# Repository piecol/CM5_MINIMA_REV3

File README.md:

# CM5 MINIMA REV3

## Introduction

The **CM5 MINIMA REV3** is a compact carrier board for the latest Raspberry Pi computing module 5.
It is designed for embedded applications, DIY electronics, and low-power computing projects. Unlike traditional desktop computers, the CM5 is a small, efficient system that integrates essential computing hardware onto a single board. Whether you're a hobbyist, developer, or engineer, this module provides a versatile platform for various applications, including IoT, automation, and custom hardware development.

If you're not familiar with Raspberry Pi or single-board computers (SBCs), think of the CM5 as a miniaturized computer that can handle tasks like data processing, networking, and hardware control, all while fitting in the palm of your hand. 
https://www.raspberrypi.com/products/compute-module-5/?variant=cm5-104032

Get to know the story behind the MINIMA on Hackster.io:

https://www.hackster.io/piecol/tiny-open-source-media-streamer-with-lorawan-what-a98a93

## Designed with KiCad

MINIMA was developed using KiCad, a powerful open-source Electronic Design Automation (EDA) tool. KiCad enables designers to create high-quality PCB layouts and schematics while maintaining full control over their hardware designs. By leveraging open-source tools like KiCad, the CM5 MINIMA REV3 embraces accessibility, collaboration, and innovation in hardware development.

## NextPCB production ready

This project is kindly supported by [NextPCB](https://www.nextpcb.com/), an excellent KiCAD-friendly PCB manufacturer.
Under "nextpcb/production_files" you can find production files to directly place your order.
Explore thier blog https://www.nextpcb.com/blog/exploring-the-cm5-minima-rev3

## Key Features

- **USB-C Power Delivery (PD):** Supports power negotiation for efficient energy use.
- **USB 2.0 Ports:** Connect peripherals such as keyboards, mice, and external storage.
- **Gigabit Ethernet:** High-speed wired networking with a low-profile cutout magjack.
- **HDMI Port:** Output video to external displays for media playback or interface applications.
- **M.2 M Key Slot:** Supports 2230/2242 SSDs for fast storage expansion.
- **CSI/DSI Connector:** Attach camera modules or displays for vision-based applications.
- **LIS3DH STM32 Sensor:** Built-in accelerometer.
- **I2C Connector (3.3V only):** Connect low-power sensors and communication modules.
- **SPI Connector:** Supports high-speed communication with other devices.
- **Fan Connector:** Optional cooling support for high-performance applications.
- **Status LEDs:** Visual indicators for power and system activity.
- **Compact Size:** Measuring only **5.4 × 5.7 cm**, ideal for space-constrained projects.

## Schematics

[PDF SCHEMATICS](https://github.com/piecol/CM5_MINIMA_REV3/blob/main/CM5_MINIMA_3.pdf)

## Getting Started

To use the **CM5 MINIMA REV3**, you'll need:

- A **USB-C power adapter** that supports Power Delivery (PD).
- A **display (HDMI)** and **input devices (USB keyboard/mouse)** for setup.
- A **network connection** (Ethernet or Wi-Fi via an external adapter if needed).

## Flashing OS

To flash an operating system (OS) to the CM5, use the switch located on the bottom of the board to enable flashing mode. It is equivalent to the "Fit nRPI_BOOT to J2 (disable eMMC Boot) on the IO board jumper." on the CM5 IO board.
Please refere to the official guidelines for further instructions:
https://www.raspberrypi.com/documentation/computers/compute-module.html#set-up-the-io-board

## Applications

- **IoT & Smart Devices:** Use sensors and network capabilities to create connected applications.
- **Home Automation:** Control and monitor home devices with minimal power consumption.
- **Embedded Systems:** Develop custom hardware solutions for industrial and consumer electronics.
- **Media Centers:** Play videos and manage digital content on an external display.
- **DIY Projects:** Ideal for makers and educators learning about electronics and programming.

## CNC casing

Custom casing with passive heat-sink was supported by PCBway, grab the .STEP file in the CNC_enclosure folder and order yours.

## Conclusion

The **CM5 MINIMA REV3** is a powerful and flexible computing module that opens up endless possibilities for embedded computing and automation. Whether you're building a smart device, experimenting with sensors, or designing a networked system, this board provides the essential features you need in a compact, energy-efficient form factor.

## **Stackup**:
6L (SIG:PWR | GND | SIG-PWR | PWR | GND | SIG:PWR) 

### If you would like to support me:

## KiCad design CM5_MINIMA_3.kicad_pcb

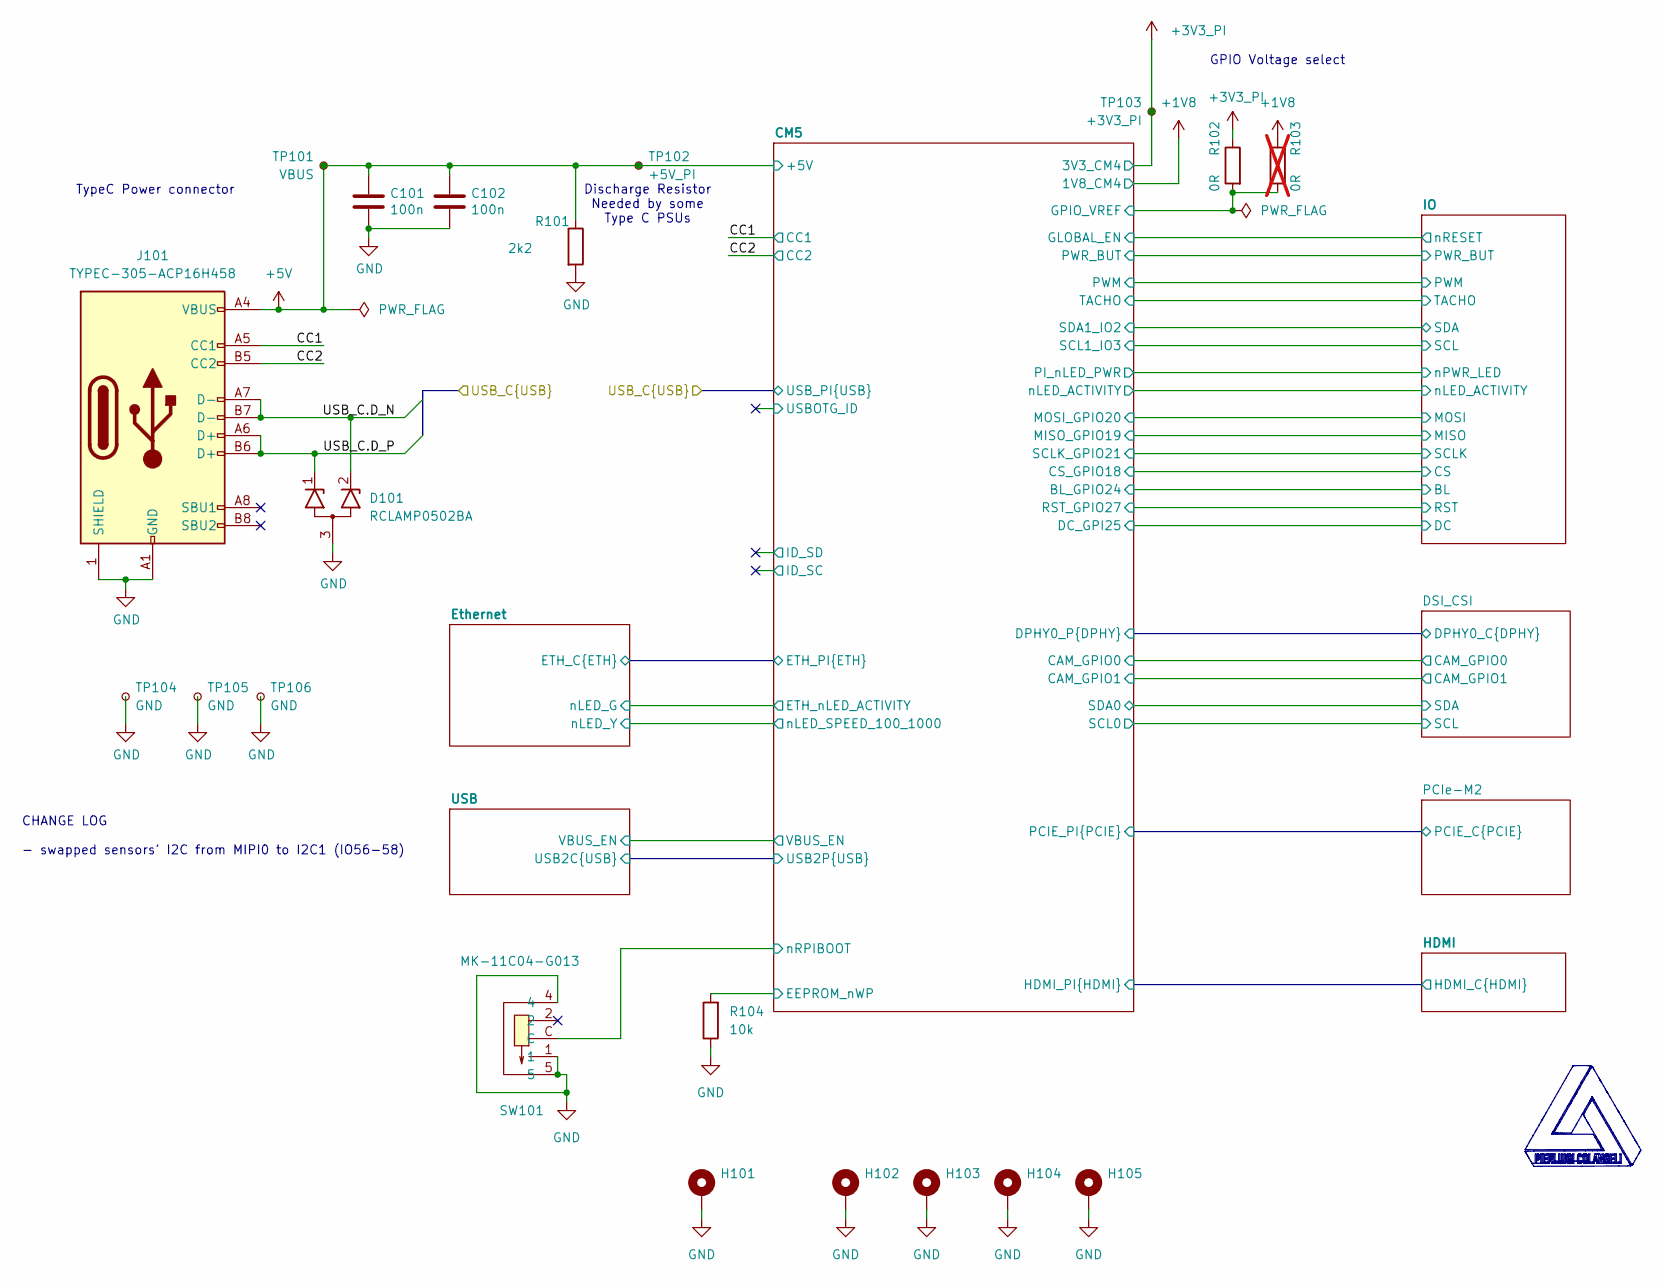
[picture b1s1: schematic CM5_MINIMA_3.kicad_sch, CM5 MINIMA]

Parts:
C101, C102: 100n; C_0402_1005Metric; Part Description 0.1uF 10% 16V Ceramic Capacitor X7R 040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
D101: RCLAMP0502BA; SOT-416
H101: MountingHole_Pad; MountingHole_2.2mm_M2_DIN965_Pad_TopBottom
H102, H103, H104, H105: MountingHole_Pad; MountingHole_2.7mm_Pad
J101: TYPEC-305-ACP16H458; USB-C-SMD_TYPEC-305-ACP16H458; Part Description USBC USB2 data and power connector
R101: 2k2; R_0402_1005Metric
R102: 0R; R_0402_1005Metric; Part Description Resistor 0R M2012 5%
R103: 0R; R_0402_1005Metric; not fitted
R104: 10k; R_0402_1005Metric
SW101: MK-11C04-G013; SW-SMD_MK-11C04-G013; LCSC Part C778185
TP101: VBUS; TestPoint_Pad_D1.0mm
TP102: +5V_PI; TestPoint_Pad_D1.0mm
TP103: +3V3_PI; TestPoint_Pad_D1.0mm
TP104, TP105, TP106: GND; TestPoint_THTPad_D1.0mm_Drill0.5mm

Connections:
+1V8: R103.1; also elsewhere on the board
+3V3_PI: R102.1, TP103.1; also elsewhere on the board
+5V: C101.1, C102.1, J101.A4 (VBUS), J101.A9 (VBUS), J101.B4 (VBUS), J101.B9 (VBUS), R101.1, TP101.1, TP102.1; also elsewhere on the board
/CC1: J101.A5 (CC1); also elsewhere on the board
/CC2: J101.B5 (CC2); also elsewhere on the board
/CM5/EEPROM_nWP: R104.2; also elsewhere on the board
/CM5/GPIO_VREF: R102.2, R103.2; also elsewhere on the board
/CM5/nRPIBOOT: SW101.C; also elsewhere on the board
/USB_C.D_N: D101.2 (K2), J101.A7 (D-), J101.B7 (D-); also elsewhere on the board
/USB_C.D_P: D101.1 (K1), J101.A6 (D+), J101.B6 (D+); also elsewhere on the board
GND: C101.2, C102.2, D101.3 (A), H101.1, H102.1, H103.1, H104.1, H105.1, J101.1 (SHIELD), J101.A1 (GND), J101.A12 (GND), J101.B1 (GND), J101.B12 (GND), R101.2, R104.1, SW101.1, SW101.4, SW101.5, TP104.1, TP105.1, TP106.1; also elsewhere on the board

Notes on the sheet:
CHANGE LOG - swapped sensors' I2C from MIPI0 to I2C1 (IO56-58)
GPIO Voltage select
TypeC Power connector
Discharge Resistor Needed by some Type C PSUs

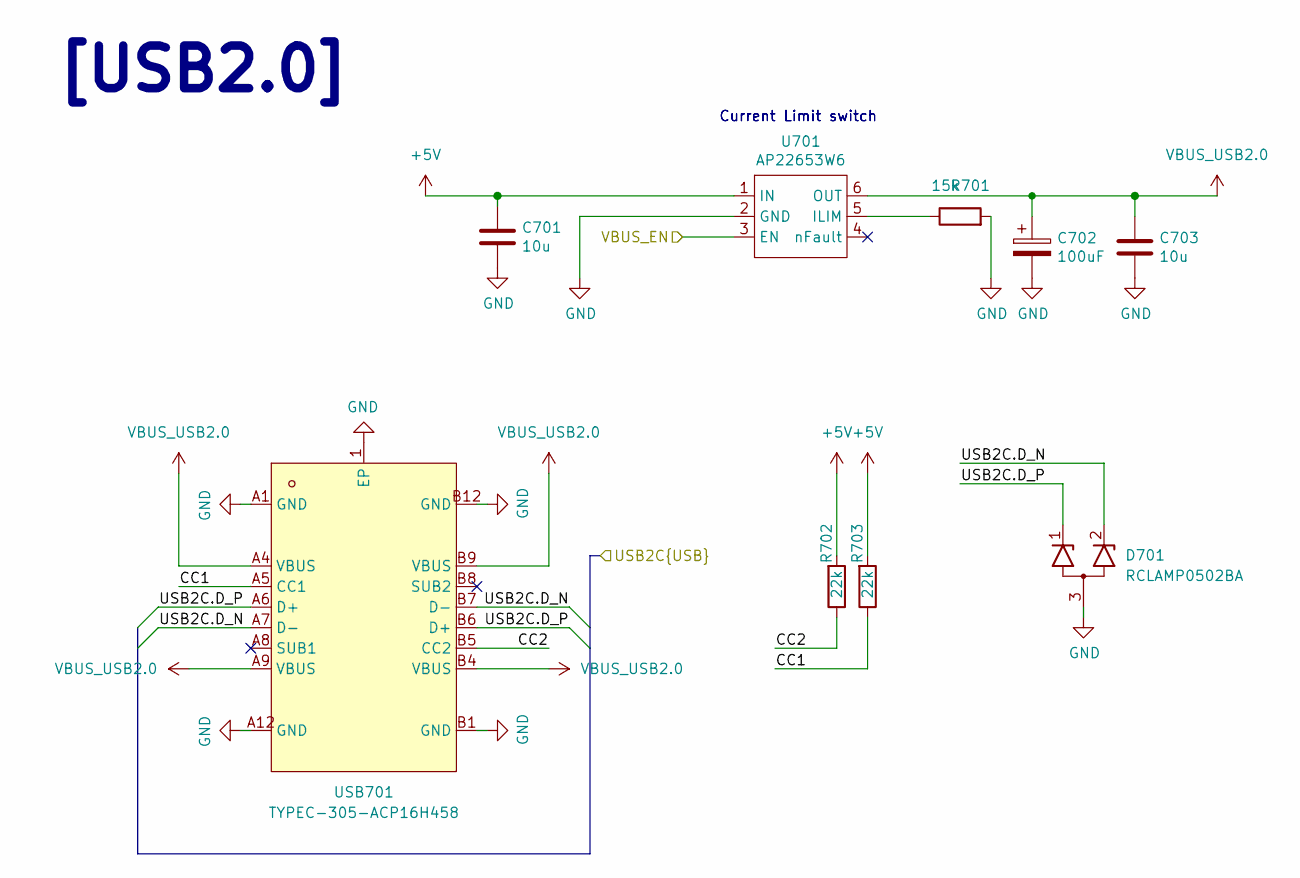
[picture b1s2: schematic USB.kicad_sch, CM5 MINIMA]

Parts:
C701, C703: 10u; C_0805_2012Metric; Part Description 10uF 10% 10V Ceramic Capacitor X7R 0805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
C702: 100uF; CP_EIA-3528-21_Kemet-B; Part Description 100uF 6.3V 1.7Ω@100kHz ±10% CASE-B-3528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
D701: RCLAMP0502BA; SOT-416
R701: 15k; R_0402_1005Metric; Part Description Resistor 15K M1005 1% 63mW
R702, R703: 22k; R_0402_1005Metric
U701: AP22653W6; SOT-23-6; Part Description Power Switch/Driver 1:1 P-Channel 2.1A 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
USB701: TYPEC-305-ACP16H458; USB-C-SMD_TYPEC-305-ACP16H458; LCSC Part C5454943

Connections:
+5V: C701.1, R702.2, R703.2, U701.1 (IN); also elsewhere on the board
/CM5/USB2P.D_N: D701.2 (K2), USB701.A7 (D-), USB701.B7 (D-); also elsewhere on the board
/CM5/USB2P.D_P: D701.1 (K1), USB701.A6 (D+), USB701.B6 (D+); also elsewhere on the board
/CM5/VBUS_EN: U701.3 (EN); also elsewhere on the board
/USB/CC1: R703.1, USB701.A5 (CC1)
/USB/CC2: R702.1, USB701.B5 (CC2)
GND: C701.2, C702.2, C703.2, D701.3 (A), R701.2, U701.2 (GND), USB701.1 (EP), USB701.A1 (GND), USB701.A12 (GND), USB701.B1 (GND), USB701.B12 (GND); also elsewhere on the board
unnamed: R701.1, U701.5 (ILIM)
VBUS_USB2.0: C702.1, C703.1, U701.6 (OUT), USB701.A4 (VBUS), USB701.A9 (VBUS), USB701.B4 (VBUS), USB701.B9 (VBUS)

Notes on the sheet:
[USB2.0]
Current Limit switch

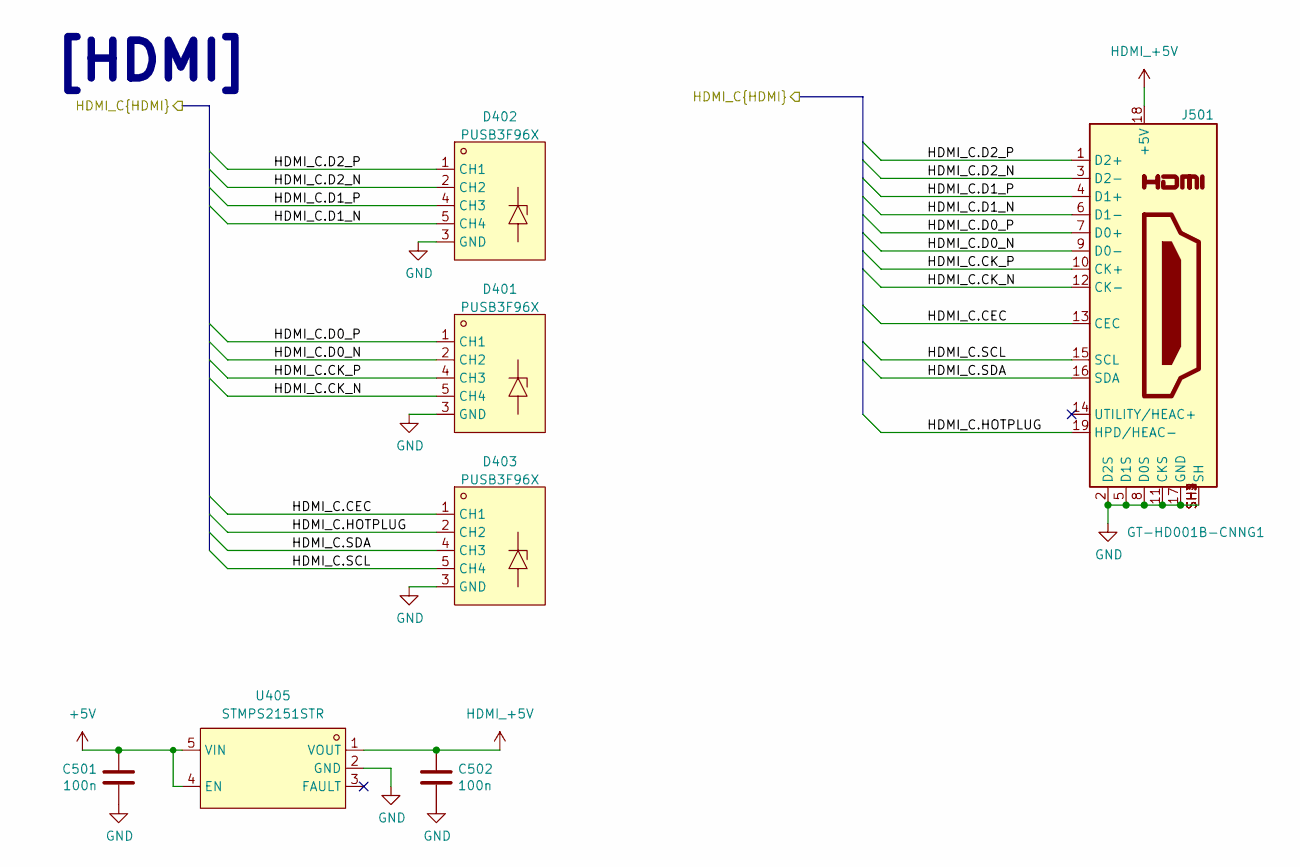
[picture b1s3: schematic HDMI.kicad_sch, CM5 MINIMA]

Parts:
C501, C502: 100n; C_0402_1005Metric; Part Description 0.1uF 10% 16V Ceramic Capacitor X7R 040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
D401, D402, D403: PUSB3F96X; DFN2510A-10_L2.5-W1.0-P0.50-BL; LCSC Part C478121
J501: GT-HD001B-CNNG1; EDAC 690-019-298-412; Part Description HDMI Connector, Right Angle, 19 Contact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
U405: STMPS2151STR; SOT-23-5; LCSC Part C135998

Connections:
+5V: C501.1, U405.4 (EN), U405.5 (VIN); also elsewhere on the board
/CM5/HDMI_PI.CEC: D403.1 (CH1), D403.10 (NC), J501.13 (CEC); also elsewhere on the board
/CM5/HDMI_PI.CK_N: D401.5 (CH4), D401.6 (NC), J501.12 (CK-); also elsewhere on the board
/CM5/HDMI_PI.CK_P: D401.4 (CH3), D401.7 (NC), J501.10 (CK+); also elsewhere on the board
/CM5/HDMI_PI.D0_N: D401.2 (CH2), D401.9 (NC), J501.9 (D0-); also elsewhere on the board
/CM5/HDMI_PI.D0_P: D401.1 (CH1), D401.10 (NC), J501.7 (D0+); also elsewhere on the board
/CM5/HDMI_PI.D1_N: D402.5 (CH4), D402.6 (NC), J501.6 (D1-); also elsewhere on the board
/CM5/HDMI_PI.D1_P: D402.4 (CH3), D402.7 (NC), J501.4 (D1+); also elsewhere on the board
/CM5/HDMI_PI.D2_N: D402.2 (CH2), D402.9 (NC), J501.3 (D2-); also elsewhere on the board
/CM5/HDMI_PI.D2_P: D402.1 (CH1), D402.10 (NC), J501.1 (D2+); also elsewhere on the board
/CM5/HDMI_PI.HOTPLUG: D403.2 (CH2), D403.9 (NC), J501.19 (HPD/HEAC-); also elsewhere on the board
/CM5/HDMI_PI.SCL: D403.5 (CH4), D403.6 (NC), J501.15 (SCL); also elsewhere on the board
/CM5/HDMI_PI.SDA: D403.4 (CH3), D403.7 (NC), J501.16 (SDA); also elsewhere on the board
GND: C501.2, C502.2, D401.3 (GND), D401.8 (GND), D402.3 (GND), D402.8 (GND), D403.3 (GND), D403.8 (GND), J501.2 (D2S), J501.5 (D1S), J501.8 (D0S), J501.11 (CKS), J501.17 (GND), J501.SH1 (SH), J501.SH2 (SH), J501.SH3 (SH), J501.SH4 (SH), U405.2 (GND); also elsewhere on the board
HDMI_+5V: C502.1, J501.18 (+5V), U405.1 (VOUT)

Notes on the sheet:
[HDMI]

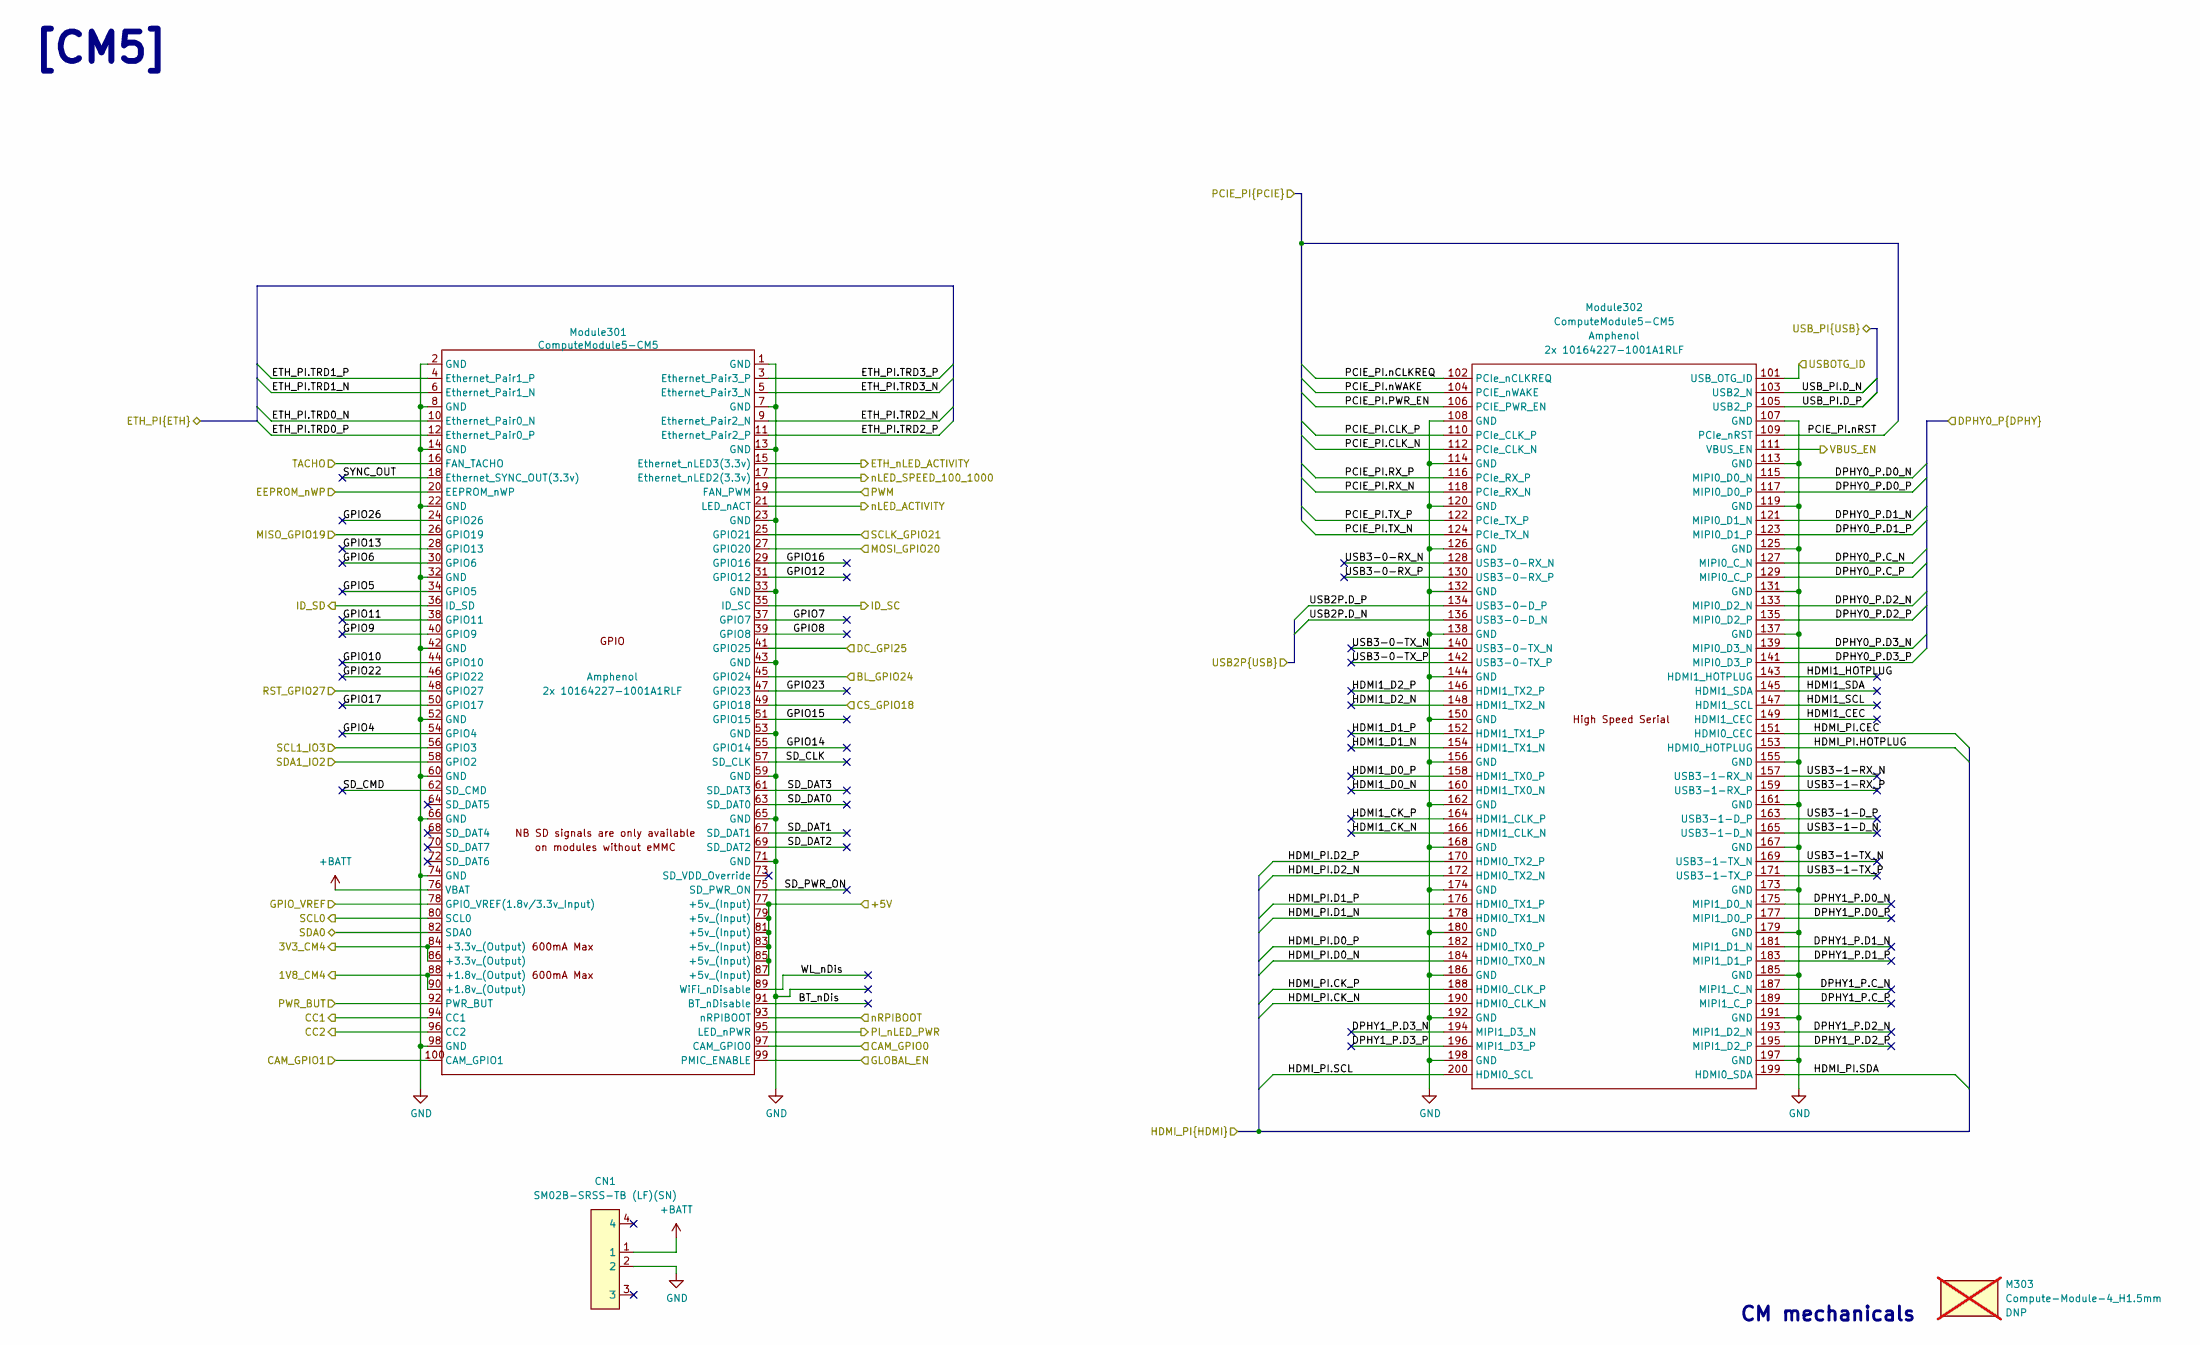
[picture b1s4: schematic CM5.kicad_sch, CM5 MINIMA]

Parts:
CN1: SM02B-SRSS-TB (LF)(SN); CONN-SMD_2P-P1.00_SM02B-SRSS-TB-LF-SN; LCSC Part C160402
M303: Compute-Module-4_H1.5mm; MPN SC0294; not fitted
Module301: ComputeModule5-CM5; Raspberry-Pi-5-Compute-Module_GPIO; Part Description 100 Position Connector Receptacle, Cent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
Module302: ComputeModule5-CM5; Raspberry-Pi-5-Compute-Module_HSS; Part Description 100 Position Connector Receptacle, Cent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

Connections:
+1V8: Module301.88 (+1.8v_(Output)), Module301.90 (+1.8v_(Output)); also elsewhere on the board
+3V3_PI: Module301.84 (+3.3v_(Output)), Module301.86 (+3.3v_(Output)); also elsewhere on the board
+5V: Module301.77 (+5v_(Input)), Module301.79 (+5v_(Input)), Module301.81 (+5v_(Input)), Module301.83 (+5v_(Input)), Module301.85 (+5v_(Input)), Module301.87 (+5v_(Input)); also elsewhere on the board
+BATT: CN1.1, Module301.76 (VBAT)
/CC1: Module301.94 (CC1); also elsewhere on the board
/CC2: Module301.96 (CC2); also elsewhere on the board
/CM5/BL_GPIO24: Module301.45 (GPIO24); also elsewhere on the board
/CM5/BT_nDis: Module301.91 (BT_nDisable)
/CM5/CAM_GPIO0: Module301.97 (CAM_GPIO0); also elsewhere on the board
/CM5/CAM_GPIO1: Module301.100 (CAM_GPIO1); also elsewhere on the board
/CM5/CS_GPIO18: Module301.49 (GPIO18); also elsewhere on the board
/CM5/DC_GPI25: Module301.41 (GPIO25); also elsewhere on the board
/CM5/DPHY0_P.C_N: Module302.127 (MIPI0_C_N); also elsewhere on the board
/CM5/DPHY0_P.C_P: Module302.129 (MIPI0_C_P); also elsewhere on the board
/CM5/DPHY0_P.D0_N: Module302.115 (MIPI0_D0_N); also elsewhere on the board
/CM5/DPHY0_P.D0_P: Module302.117 (MIPI0_D0_P); also elsewhere on the board
/CM5/DPHY0_P.D1_N: Module302.121 (MIPI0_D1_N); also elsewhere on the board
/CM5/DPHY0_P.D1_P: Module302.123 (MIPI0_D1_P); also elsewhere on the board
/CM5/DPHY0_P.D2_N: Module302.133 (MIPI0_D2_N); also elsewhere on the board
/CM5/DPHY0_P.D2_P: Module302.135 (MIPI0_D2_P); also elsewhere on the board
/CM5/DPHY0_P.D3_N: Module302.139 (MIPI0_D3_N); also elsewhere on the board
/CM5/DPHY0_P.D3_P: Module302.141 (MIPI0_D3_P); also elsewhere on the board
/CM5/DPHY1_P.C_N: Module302.187 (MIPI1_C_N)
/CM5/DPHY1_P.C_P: Module302.189 (MIPI1_C_P)
/CM5/DPHY1_P.D0_N: Module302.175 (MIPI1_D0_N)
/CM5/DPHY1_P.D0_P: Module302.177 (MIPI1_D0_P)
/CM5/DPHY1_P.D1_N: Module302.181 (MIPI1_D1_N)
/CM5/DPHY1_P.D1_P: Module302.183 (MIPI1_D1_P)
/CM5/DPHY1_P.D2_N: Module302.193 (MIPI1_D2_N)
/CM5/DPHY1_P.D2_P: Module302.195 (MIPI1_D2_P)
/CM5/DPHY1_P.D3_N: Module302.194 (MIPI1_D3_N)
/CM5/DPHY1_P.D3_P: Module302.196 (MIPI1_D3_P)
/CM5/EEPROM_nWP: Module301.20 (EEPROM_nWP); also elsewhere on the board
/CM5/ETH_PI.TRD0_N: Module301.10 (Ethernet_Pair0_N); also elsewhere on the board
/CM5/ETH_PI.TRD0_P: Module301.12 (Ethernet_Pair0_P); also elsewhere on the board
/CM5/ETH_PI.TRD1_N: Module301.6 (Ethernet_Pair1_N); also elsewhere on the board
/CM5/ETH_PI.TRD1_P: Module301.4 (Ethernet_Pair1_P); also elsewhere on the board
/CM5/ETH_PI.TRD2_N: Module301.9 (Ethernet_Pair2_N); also elsewhere on the board
/CM5/ETH_PI.TRD2_P: Module301.11 (Ethernet_Pair2_P); also elsewhere on the board
/CM5/ETH_PI.TRD3_N: Module301.5 (Ethernet_Pair3_N); also elsewhere on the board
/CM5/ETH_PI.TRD3_P: Module301.3 (Ethernet_Pair3_P); also elsewhere on the board
/CM5/ETH_nLED_ACTIVITY: Module301.15 (Ethernet_nLED3(3.3v)); also elsewhere on the board
/CM5/GLOBAL_EN: Module301.99 (PMIC_ENABLE)
/CM5/GPIO4: Module301.54 (GPIO4)
/CM5/GPIO5: Module301.34 (GPIO5)
/CM5/GPIO6: Module301.30 (GPIO6)
/CM5/GPIO7: Module301.37 (GPIO7)
/CM5/GPIO8: Module301.39 (GPIO8)
/CM5/GPIO9: Module301.40 (GPIO9)
/CM5/GPIO10: Module301.44 (GPIO10)
/CM5/GPIO11: Module301.38 (GPIO11)
/CM5/GPIO12: Module301.31 (GPIO12)
/CM5/GPIO13: Module301.28 (GPIO13)
/CM5/GPIO14: Module301.55 (GPIO14)
/CM5/GPIO15: Module301.51 (GPIO15)
/CM5/GPIO16: Module301.29 (GPIO16)
/CM5/GPIO17: Module301.50 (GPIO17)
/CM5/GPIO22: Module301.46 (GPIO22)
/CM5/GPIO23: Module301.47 (GPIO23)
/CM5/GPIO26: Module301.24 (GPIO26)
/CM5/GPIO_VREF: Module301.78 (GPIO_VREF(1.8v/3.3v_Input)); also elsewhere on the board
/CM5/HDMI1_CEC: Module302.149 (HDMI1_CEC)
/CM5/HDMI1_CK_N: Module302.166 (HDMI1_CLK_N)
/CM5/HDMI1_CK_P: Module302.164 (HDMI1_CLK_P)
/CM5/HDMI1_D0_N: Module302.160 (HDMI1_TX0_N)
/CM5/HDMI1_D0_P: Module302.158 (HDMI1_TX0_P)
/CM5/HDMI1_D1_N: Module302.154 (HDMI1_TX1_N)
/CM5/HDMI1_D1_P: Module302.152 (HDMI1_TX1_P)
/CM5/HDMI1_D2_N: Module302.148 (HDMI1_TX2_N)
/CM5/HDMI1_D2_P: Module302.146 (HDMI1_TX2_P)
/CM5/HDMI1_HOTPLUG: Module302.143 (HDMI1_HOTPLUG)
/CM5/HDMI1_SCL: Module302.147 (HDMI1_SCL)
/CM5/HDMI1_SDA: Module302.145 (HDMI1_SDA)
/CM5/HDMI_PI.CEC: Module302.151 (HDMI0_CEC); also elsewhere on the board
/CM5/HDMI_PI.CK_N: Module302.190 (HDMI0_CLK_N); also elsewhere on the board
/CM5/HDMI_PI.CK_P: Module302.188 (HDMI0_CLK_P); also elsewhere on the board
/CM5/HDMI_PI.D0_N: Module302.184 (HDMI0_TX0_N); also elsewhere on the board
/CM5/HDMI_PI.D0_P: Module302.182 (HDMI0_TX0_P); also elsewhere on the board
/CM5/HDMI_PI.D1_N: Module302.178 (HDMI0_TX1_N); also elsewhere on the board
/CM5/HDMI_PI.D1_P: Module302.176 (HDMI0_TX1_P); also elsewhere on the board
/CM5/HDMI_PI.D2_N: Module302.172 (HDMI0_TX2_N); also elsewhere on the board
/CM5/HDMI_PI.D2_P: Module302.170 (HDMI0_TX2_P); also elsewhere on the board
/CM5/HDMI_PI.HOTPLUG: Module302.153 (HDMI0_HOTPLUG); also elsewhere on the board
/CM5/HDMI_PI.SCL: Module302.200 (HDMI0_SCL); also elsewhere on the board
/CM5/HDMI_PI.SDA: Module302.199 (HDMI0_SDA); also elsewhere on the board
/CM5/ID_SC: Module301.35 (ID_SC)
/CM5/ID_SD: Module301.36 (ID_SD)
/CM5/MISO_GPIO19: Module301.26 (GPIO19); also elsewhere on the board
/CM5/MOSI_GPIO20: Module301.27 (GPIO20); also elsewhere on the board
/CM5/PCIE_PI.CLK_N: Module302.112 (PCIe_CLK_N); also elsewhere on the board
/CM5/PCIE_PI.CLK_P: Module302.110 (PCIe_CLK_P); also elsewhere on the board
/CM5/PCIE_PI.PWR_EN: Module302.106 (PCIE_PWR_EN); also elsewhere on the board
/CM5/PCIE_PI.RX_N: Module302.118 (PCIe_RX_N); also elsewhere on the board
/CM5/PCIE_PI.RX_P: Module302.116 (PCIe_RX_P); also elsewhere on the board
/CM5/PCIE_PI.TX_N: Module302.124 (PCIe_TX_N); also elsewhere on the board
/CM5/PCIE_PI.TX_P: Module302.122 (PCIe_TX_P); also elsewhere on the board
/CM5/PCIE_PI.nCLKREQ: Module302.102 (PCIe_nCLKREQ); also elsewhere on the board
/CM5/PCIE_PI.nRST: Module302.109 (PCIe_nRST); also elsewhere on the board
/CM5/PCIE_PI.nWAKE: Module302.104 (PCIE_nWAKE); also elsewhere on the board
/CM5/PI_nLED_PWR: Module301.95 (LED_nPWR); also elsewhere on the board
/CM5/PWM: Module301.19 (FAN_PWM); also elsewhere on the board
/CM5/PWR_BUT: Module301.92 (PWR_BUT); also elsewhere on the board
/CM5/RST_GPIO27: Module301.48 (GPIO27); also elsewhere on the board
/CM5/SCL0: Module301.80 (SCL0); also elsewhere on the board
/CM5/SCLK_GPIO21: Module301.25 (GPIO21); also elsewhere on the board
/CM5/SDA0: Module301.82 (SDA0); also elsewhere on the board
/CM5/SD_CLK: Module301.57 (SD_CLK)
/CM5/SD_CMD: Module301.62 (SD_CMD)
/CM5/SD_DAT0: Module301.63 (SD_DAT0)
/CM5/SD_DAT1: Module301.67 (SD_DAT1)
/CM5/SD_DAT2: Module301.69 (SD_DAT2)
/CM5/SD_DAT3: Module301.61 (SD_DAT3)
/CM5/SD_PWR_ON: Module301.75 (SD_PWR_ON)
/CM5/SYNC_OUT: Module301.18 (Ethernet_SYNC_OUT(3.3v))
/CM5/TACHO: Module301.16 (FAN_TACHO); also elsewhere on the board
/CM5/USB2P.D_N: Module302.136 (USB3-0-D_N); also elsewhere on the board
/CM5/USB2P.D_P: Module302.134 (USB3-0-D_P); also elsewhere on the board
/CM5/USB3-0-RX_N: Module302.128 (USB3-0-RX_N)
/CM5/USB3-0-RX_P: Module302.130 (USB3-0-RX_P)
/CM5/USB3-0-TX_N: Module302.140 (USB3-0-TX_N)
/CM5/USB3-0-TX_P: Module302.142 (USB3-0-TX_P)
/CM5/USB3-1-D_N: Module302.165 (USB3-1-D_N)
/CM5/USB3-1-D_P: Module302.163 (USB3-1-D_P)
/CM5/USB3-1-RX_N: Module302.157 (USB3-1-RX_N)
/CM5/USB3-1-RX_P: Module302.159 (USB3-1-RX_P)
/CM5/USB3-1-TX_N: Module302.169 (USB3-1-TX_N)
/CM5/USB3-1-TX_P: Module302.171 (USB3-1-TX_P)
/CM5/USBOTG_ID: Module302.101 (USB_OTG_ID)
/CM5/VBUS_EN: Module302.111 (VBUS_EN); also elsewhere on the board
/CM5/WL_nDis: Module301.89 (WiFi_nDisable)
/CM5/nLED_ACTIVITY: Module301.21 (LED_nACT); also elsewhere on the board
/CM5/nLED_SPEED_100_1000: Module301.17 (Ethernet_nLED2(3.3v)); also elsewhere on the board
/CM5/nRPIBOOT: Module301.93 (nRPIBOOT); also elsewhere on the board
/IO/SCL: Module301.56 (GPIO3); also elsewhere on the board
/IO/SDA: Module301.58 (GPIO2); also elsewhere on the board
/USB_C.D_N: Module302.103 (USB2_N); also elsewhere on the board
/USB_C.D_P: Module302.105 (USB2_P); also elsewhere on the board
GND: CN1.2, Module301.1 (GND), Module301.2 (GND), Module301.7 (GND), Module301.8 (GND), Module301.13 (GND), Module301.14 (GND), Module301.22 (GND), Module301.23 (GND), Module301.32 (GND), Module301.33 (GND), Module301.42 (GND), Module301.43 (GND), Module301.52 (GND), Module301.53 (GND), Module301.59 (GND), Module301.60 (GND), Module301.65 (GND), Module301.66 (GND), Module301.71 (GND), Module301.74 (GND), Module301.98 (GND), Module302.107 (GND), Module302.108 (GND), Module302.113 (GND), Module302.114 (GND), Module302.119 (GND), Module302.120 (GND), Module302.125 (GND), Module302.126 (GND), Module302.131 (GND), Module302.132 (GND), Module302.137 (GND), Module302.138 (GND), Module302.144 (GND), Module302.150 (GND), Module302.155 (GND), Module302.156 (GND), Module302.161 (GND), Module302.162 (GND), Module302.167 (GND), Module302.168 (GND), Module302.173 (GND), Module302.174 (GND), Module302.179 (GND), Module302.180 (GND), Module302.185 (GND), Module302.186 (GND), Module302.191 (GND), Module302.192 (GND), Module302.197 (GND), Module302.198 (GND); also elsewhere on the board

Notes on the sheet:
CM mechanicals
[CM5]

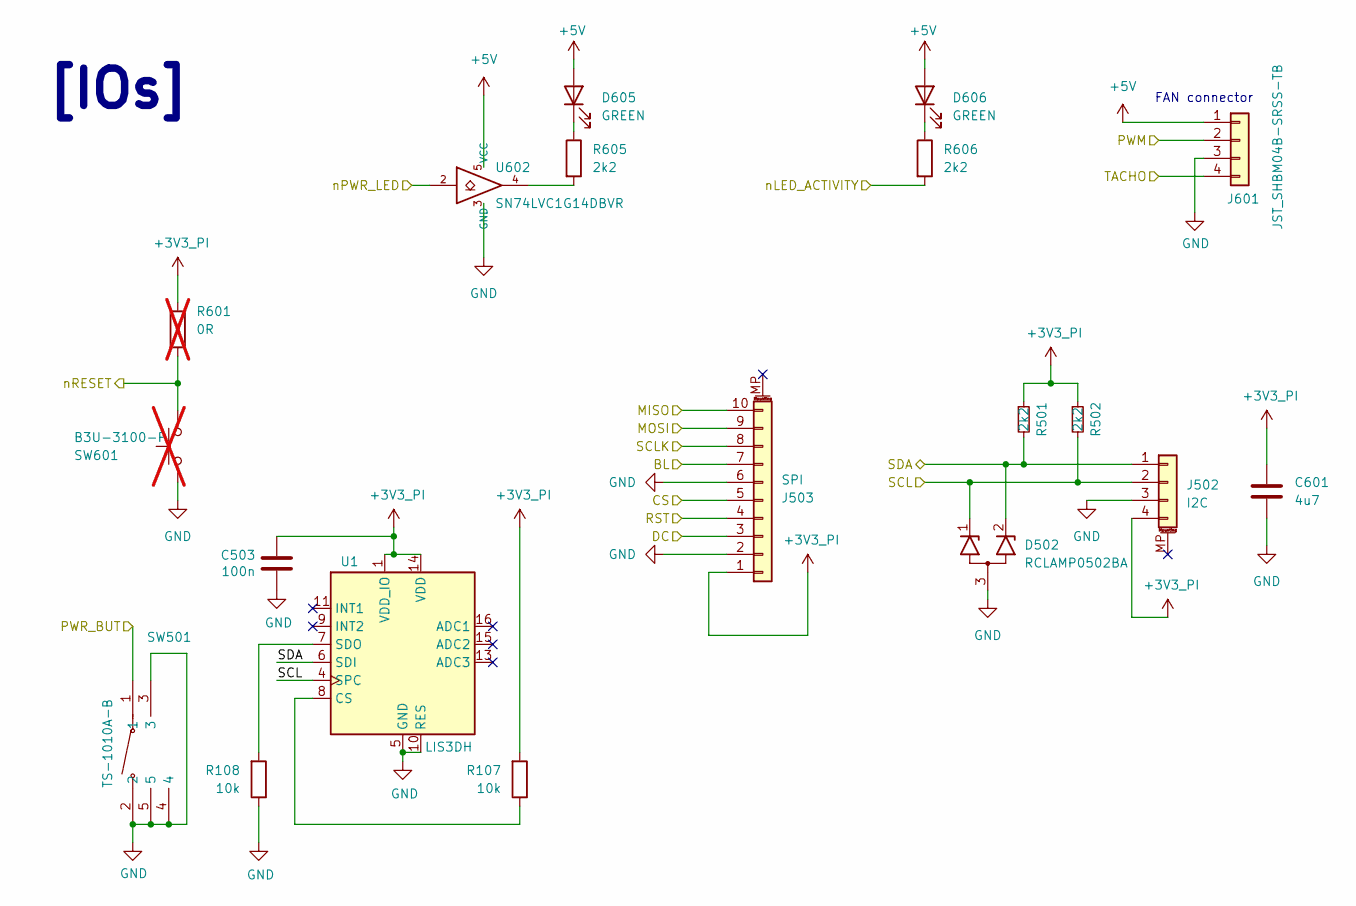
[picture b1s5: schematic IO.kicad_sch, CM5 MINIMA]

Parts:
C503: 100n; C_0402_1005Metric; Part Description 0.1uF 10% 16V Ceramic Capacitor X7R 040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
C601: 4u7; C_0805_2012Metric; Part Description 4.7uF 10% 10V Ceramic Capacitor X7R 080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
D502: RCLAMP0502BA; SOT-416
D605, D606: GREEN; LED-SMD_L1.7-W0.6-RD
J502: I2C; JST_SH_BM04B-SRSS-TB_1x04-1MP_P1.00mm_Vertical
J503: SPI; JST_SUR_BM10B-SURS-TF_1x10-1MP_P0.80mm_Vertical
J601: JST_SHBM04B-SRSS-TB; JST_SH_BM04B-SRSS-TB_1x04-1MP_P1.00mm_Vertical; Part Description 4 pin vertical 1mm pitch connector
R107, R108: 10k; R_0402_1005Metric
R501, R502, R605, R606: 2k2; R_0402_1005Metric
R601: 0R; R_0402_1005Metric; not fitted
SW501: TS-1010A-B; SW-SMD_TS-1010A-B; LCSC Part C381059
SW601: B3U-3100-P; SW_SPST_B3U-3100P-B; not fitted
U1: LIS3DH; LGA-16_3x3mm_P0.5mm_LayoutBorder3x5y
U602: SN74LVC1G14DBVR; SOT-353_SC-70-5; Part Description Buffer, Non-Inverting 1 Element 1 Bit p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

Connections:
+3V3_PI: C503.1, C601.1, J502.4, J503.1, R107.2, R501.1, R502.1, R601.1, U1.1 (VDD_IO), U1.14 (VDD); also elsewhere on the board
+5V: D605.2 (A), D606.2 (A), J601.1, U602.5 (VCC); also elsewhere on the board
/CM5/BL_GPIO24: J503.7; also elsewhere on the board
/CM5/CS_GPIO18: J503.5; also elsewhere on the board
/CM5/DC_GPI25: J503.3; also elsewhere on the board
/CM5/MISO_GPIO19: J503.10; also elsewhere on the board
/CM5/MOSI_GPIO20: J503.9; also elsewhere on the board
/CM5/PI_nLED_PWR: U602.2; also elsewhere on the board
/CM5/PWM: J601.2; also elsewhere on the board
/CM5/PWR_BUT: SW501.1; also elsewhere on the board
/CM5/RST_GPIO27: J503.4; also elsewhere on the board
/CM5/SCLK_GPIO21: J503.8; also elsewhere on the board
/CM5/TACHO: J601.4; also elsewhere on the board
/CM5/nLED_ACTIVITY: R606.2; also elsewhere on the board
/IO/SCL: D502.1 (K1), J502.2, R502.2, U1.4 (SPC); also elsewhere on the board
/IO/SDA: D502.2 (K2), J502.1, R501.2, U1.6 (SDI); also elsewhere on the board
GND: C503.2, C601.2, D502.3 (A), J502.3, J503.2, J503.6, J601.3, R108.1, SW501.2, SW501.3, SW501.4, SW501.5, SW601.2, U1.5 (GND), U1.10 (RES), U1.12 (GND), U602.3 (GND); also elsewhere on the board
unnamed: D605.1 (K), R605.1
unnamed: D606.1 (K), R606.1
unnamed: R601.2, SW601.1
unnamed: R605.2, U602.4
unnamed: R107.1, U1.8 (CS)
unnamed: R108.2, U1.7 (SDO)

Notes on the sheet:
[IOs]
FAN connector

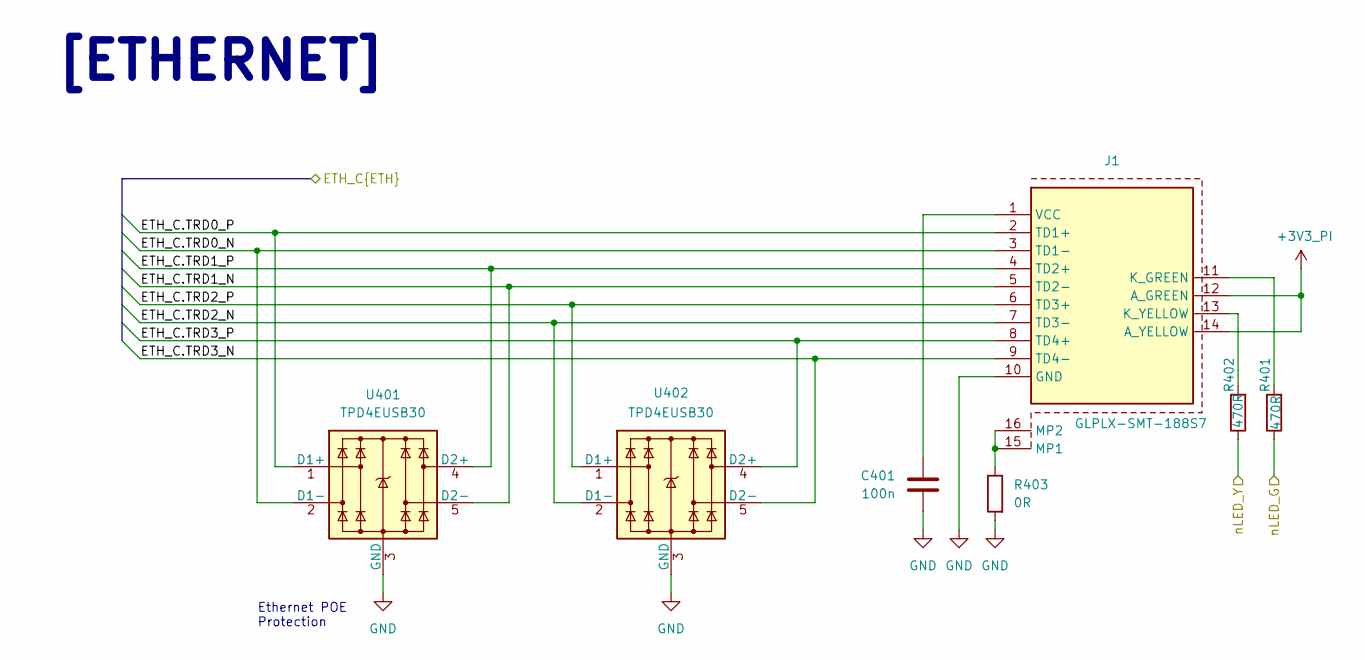
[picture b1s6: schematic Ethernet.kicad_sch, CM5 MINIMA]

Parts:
C401: 100n; C_0402_1005Metric; Part Description 0.1uF 10% 16V Ceramic Capacitor X7R 040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
J1: GLPLX-SMT-188S7; GLPLXSMT188S7QQYG; Manufacturer_Part_Number GLPLX-SMT-188S7-QQ-Y/G; Mouser Part Number 806-GLPLXSMT188S7-YG
R401, R402: 470R; R_0402_1005Metric
R403: 0R; R_0402_1005Metric
U401, U402: TPD4EUSB30; USON-10_2.5x1.0mm_P0.5mm; Part Description Quad TVS diode for high speed signals (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

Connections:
+3V3_PI: J1.12 (A_GREEN), J1.14 (A_YELLOW); also elsewhere on the board
/CM5/ETH_PI.TRD0_N: J1.3 (TD1-), U401.2 (D1-), U401.9; also elsewhere on the board
/CM5/ETH_PI.TRD0_P: J1.2 (TD1+), U401.1 (D1+), U401.10; also elsewhere on the board
/CM5/ETH_PI.TRD1_N: J1.5 (TD2-), U401.5 (D2-), U401.6; also elsewhere on the board
/CM5/ETH_PI.TRD1_P: J1.4 (TD2+), U401.4 (D2+), U401.7; also elsewhere on the board
/CM5/ETH_PI.TRD2_N: J1.7 (TD3-), U402.2 (D1-), U402.9; also elsewhere on the board
/CM5/ETH_PI.TRD2_P: J1.6 (TD3+), U402.1 (D1+), U402.10; also elsewhere on the board
/CM5/ETH_PI.TRD3_N: J1.9 (TD4-), U402.5 (D2-), U402.6; also elsewhere on the board
/CM5/ETH_PI.TRD3_P: J1.8 (TD4+), U402.4 (D2+), U402.7; also elsewhere on the board
/CM5/ETH_nLED_ACTIVITY: R401.1; also elsewhere on the board
/CM5/nLED_SPEED_100_1000: R402.1; also elsewhere on the board
GND: C401.2, J1.10 (GND), R403.2, U401.3 (GND), U401.8 (GND), U402.3 (GND), U402.8 (GND); also elsewhere on the board
unnamed: J1.11 (K_GREEN), R401.2
unnamed: J1.13 (K_YELLOW), R402.2
unnamed: J1.15 (MP1), J1.16 (MP2), R403.1
unnamed: C401.1, J1.1 (VCC)

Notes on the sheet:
[ETHERNET]
Ethernet POE Protection

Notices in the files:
parts and their libraries:
License: Apache-2.0
